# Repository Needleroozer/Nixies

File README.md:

# Nixies

A GitHub repository for collecting various Nixie tube PCB designs and the code that goes with them

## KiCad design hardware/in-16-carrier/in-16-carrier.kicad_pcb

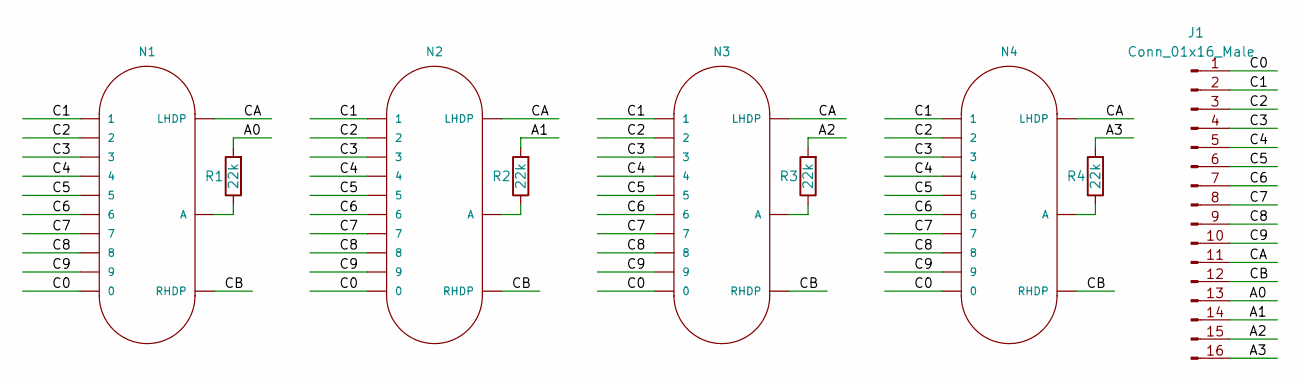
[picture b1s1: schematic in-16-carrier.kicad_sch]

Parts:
J1: Conn_01x16_Male; PinHeader_1x16_P2.54mm_Vertical
N1, N2, N3, N4: IN-16; nixies-us-IN-16
R1, R2, R3, R4: 22k; R_Axial_DIN0207_L6.3mm_D2.5mm_P10.16mm_Horizontal

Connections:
/A0: J1.13, R1.2
/A1: J1.14, R2.2
/A2: J1.15, R3.2
/A3: J1.16, R4.2
/C0: J1.1, N1.0, N2.0, N3.0, N4.0
/C1: J1.2, N1.1, N2.1, N3.1, N4.1
/C2: J1.3, N1.2, N2.2, N3.2, N4.2
/C3: J1.4, N1.3, N2.3, N3.3, N4.3
/C4: J1.5, N1.4, N2.4, N3.4, N4.4
/C5: J1.6, N1.5, N2.5, N3.5, N4.5
/C6: J1.7, N1.6, N2.6, N3.6, N4.6
/C7: J1.8, N1.7, N2.7, N3.7, N4.7
/C8: J1.9, N1.8, N2.8, N3.8, N4.8
/C9: J1.10, N1.9, N2.9, N3.9, N4.9
/CA: J1.11, N1.LHDP, N2.LHDP, N3.LHDP, N4.LHDP
/CB: J1.12, N1.RHDP, N2.RHDP, N3.RHDP, N4.RHDP
unnamed: N1.A, R1.1
unnamed: N2.A, R2.1
unnamed: N3.A, R3.1
unnamed: N4.A, R4.1

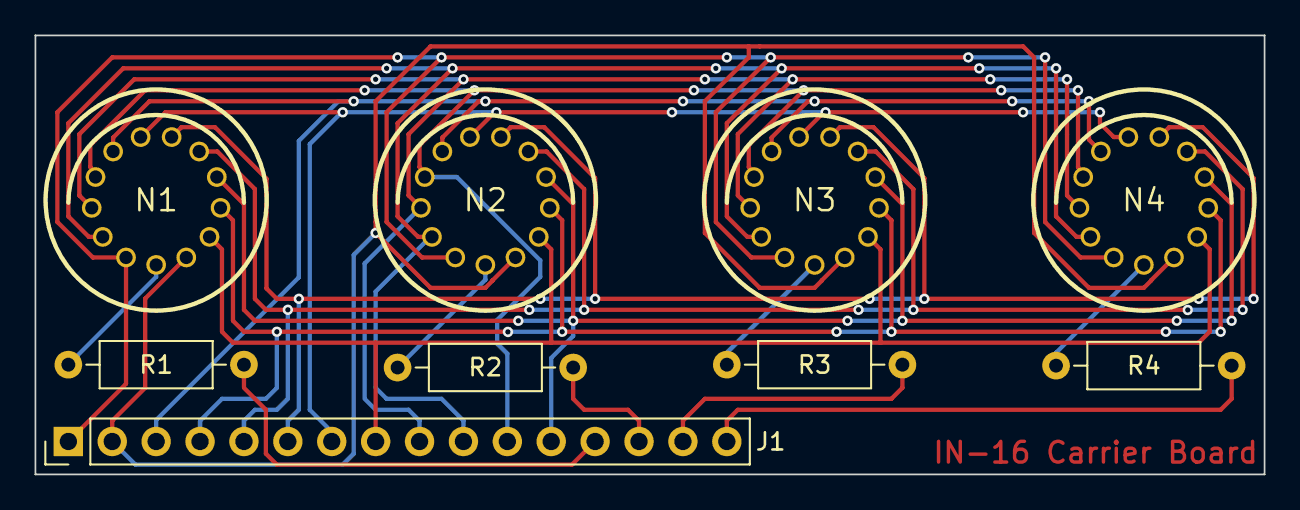
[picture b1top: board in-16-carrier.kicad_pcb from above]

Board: 2 copper layers, 71.1 x 25.4 mm, 9 parts (0 on the bottom side), 20 nets.

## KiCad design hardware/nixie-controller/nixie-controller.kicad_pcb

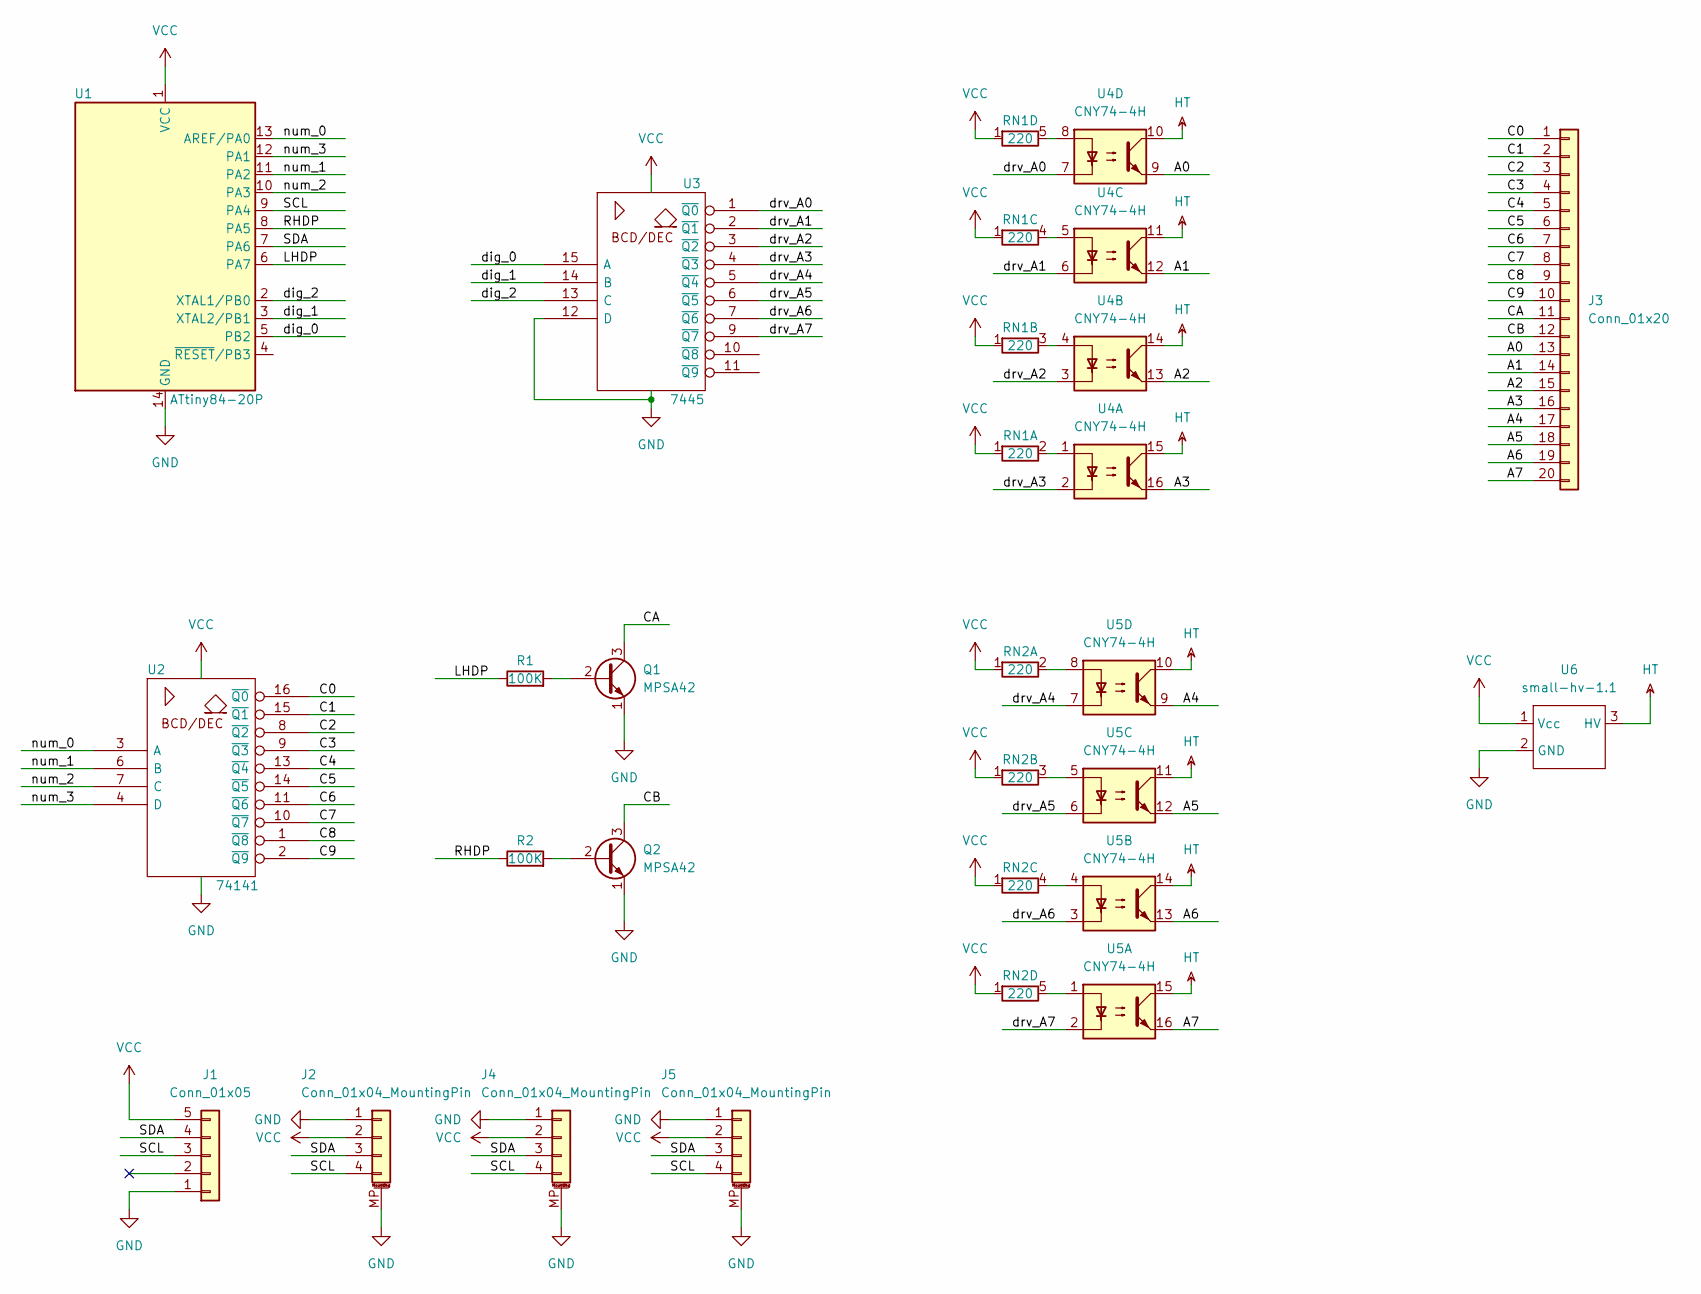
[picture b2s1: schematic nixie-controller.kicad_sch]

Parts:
J1: Conn_01x05; PinHeader_1x05_P2.54mm_Vertical
J2, J4, J5: Conn_01x04_MountingPin; JST_SH_SM04B-SRSS-TB_1x04-1MP_P1.00mm_Horizontal
J3: Conn_01x20; PinSocket_1x20_P2.54mm_Vertical
Q1, Q2: MPSA42; TO-92_Inline_Wide
R1, R2: 100K; R_Axial_DIN0207_L6.3mm_D2.5mm_P10.16mm_Horizontal
RN1, RN2: 220; R_Array_SIP5
U1: ATtiny84-20P; DIP-14_W7.62mm
U2: 74141; DIP-16_W7.62mm
U3: 7445; DIP-16_W7.62mm
U4, U5: CNY74-4H; DIP-16_W7.62mm
U6: small-hv-1.1

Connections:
/A0: J3.13, U4.9
/A1: J3.14, U4.12
/A2: J3.15, U4.13
/A3: J3.16, U4.16
/A4: J3.17, U5.9
/A5: J3.18, U5.12
/A6: J3.19, U5.13
/A7: J3.20, U5.16
/C0: J3.1, U2.16 (~Q0)
/C1: J3.2, U2.15 (~Q1)
/C2: J3.3, U2.8 (~Q2)
/C3: J3.4, U2.9 (~Q3)
/C4: J3.5, U2.13 (~Q4)
/C5: J3.6, U2.14 (~Q5)
/C6: J3.7, U2.11 (~Q6)
/C7: J3.8, U2.10 (~Q7)
/C8: J3.9, U2.1 (~Q8)
/C9: J3.10, U2.2 (~Q9)
/CA: J3.11, Q1.3 (C)
/CB: J3.12, Q2.3 (C)
/LHDP: R1.1, U1.6 (PA7)
/RHDP: R2.1, U1.8 (PA5)
/SCL: J1.3, J2.4, J4.4, J5.4, U1.9 (PA4)
/SDA: J1.4, J2.3, J4.3, J5.3, U1.7 (PA6)
/dig_0: U1.5 (PB2), U3.15 (A)
/dig_1: U1.3 (XTAL2/PB1), U3.14 (B)
/dig_2: U1.2 (XTAL1/PB0), U3.13 (C)
/drv_A0: U3.1 (~Q0), U4.7
/drv_A1: U3.2 (~Q1), U4.6
/drv_A2: U3.3 (~Q2), U4.3
/drv_A3: U3.4 (~Q3), U4.2
/drv_A4: U3.5 (~Q4), U5.7
/drv_A5: U3.6 (~Q5), U5.6
/drv_A6: U3.7 (~Q6), U5.3
/drv_A7: U3.9 (~Q7), U5.2
/num_0: U1.13 (AREF/PA0), U2.3 (A)
/num_1: U1.11 (PA2), U2.6 (B)
/num_2: U1.10 (PA3), U2.7 (C)
/num_3: U1.12 (PA1), U2.4 (D)
GND: J1.1, J2.1, J2.MP (MountPin), J4.1, J4.MP (MountPin), J5.1, J5.MP (MountPin), Q1.1 (E), Q2.1 (E), U1.14 (GND), U2.12 (GND), U3.8 (GND), U3.12 (D), U6.2 (GND)
HT: U4.10, U4.11, U4.14, U4.15, U5.10, U5.11, U5.14, U5.15, U6.3 (HV)
unnamed: Q1.2 (B), R1.2
unnamed: Q2.2 (B), R2.2
unnamed: RN1.2 (R1.2), U4.1
unnamed: RN1.3 (R2.2), U4.4
unnamed: RN1.4 (R3.2), U4.5
unnamed: RN1.5 (R4.2), U4.8
unnamed: RN2.2 (R1.2), U5.8
unnamed: RN2.3 (R2.2), U5.5
unnamed: RN2.4 (R3.2), U5.4
unnamed: RN2.5 (R4.2), U5.1
VCC: J1.5, J2.2, J4.2, J5.2, RN1.1 (R1.1), RN2.1 (R1.1), U1.1 (VCC), U2.5 (VCC), U3.16 (VCC), U6.1 (Vcc)

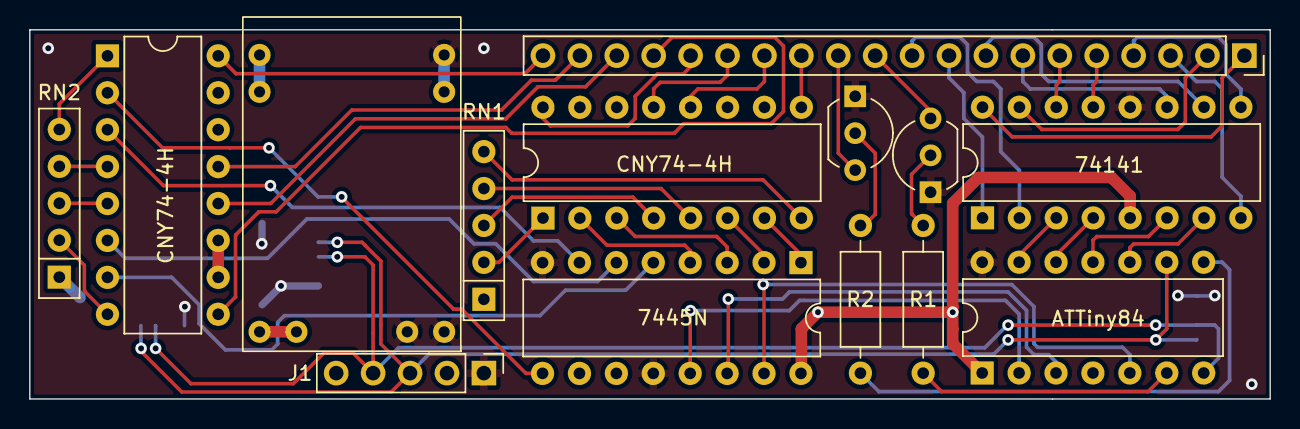
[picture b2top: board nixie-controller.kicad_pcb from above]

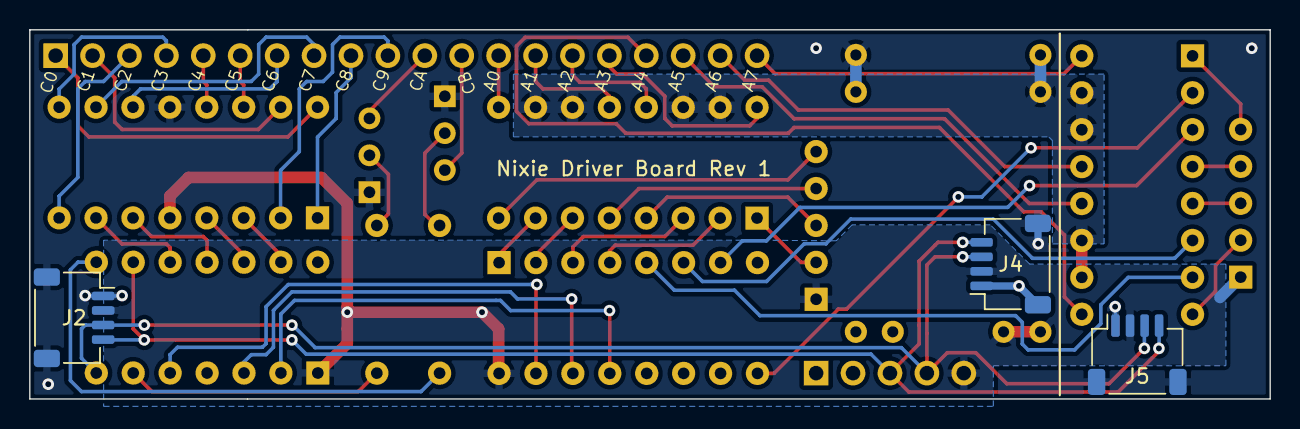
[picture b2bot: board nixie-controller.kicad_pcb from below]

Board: 2 copper layers, 85.3 x 25.4 mm, 17 parts (3 on the bottom side), 52 nets.

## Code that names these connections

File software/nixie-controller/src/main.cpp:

#include <Arduino.h>

// PB0 is bit 2
// PB1 is bit 1
// PB2 is bit 0
#define ENABLE_ANODE(num) (PORTB = (PORTB & ~0x07) | ((num & 0b01) << 2) | (num & 0b010) | ((num & 0b0100) >> 2))

// PA0 is bit 0
// PA1 is bit 3
// PA2 is bit 1
// PA3 is bit 2
#define ENABLE_CATHODE(num) (PORTA = (PORTA & ~0xF0) | ((num & 0b0100) << 1) | ((num & 0b010) << 1) | ((num & 0b1000) >> 2) | (num & 0b01))

#define DISABLE_CATHODES() (PORTA &= 0x50) 

// 7-bit I2C address
#define I2C_SLAVE_ADDRESS 0x4E

struct I2C_Regs_s {
    uint8_t digits[8];
    uint8_t decimals[8];
};

#define REG_SIZE (sizeof(I2C_Regs_s))

volatile union {
    struct I2C_Regs_s regs;
    uint8_t bytes[REG_SIZE];
} i2c_regs = { .regs = {{0xde, 0xad, 0xbe, 0xef, 0xd0, 0xd0, 0xca, 0xfe},
                        {0x01, 0x02, 0x03, 0x04, 0x05, 0x06, 0x07, 0x08}}
};


// decimal points are active-high since we're using NPN transistors
void set_dp(uint8_t val)
{
    switch(val)
    {
        case 1:
            PORTA |= (1 << PA5); // RHDP
            break;
    	case 2:
            PORTA |= (1 << PA7); // LHDP
            break;
        case 3:
            PORTA |= (1 << PA5) | (1 << PA7);
            break;
        default:
            PORTA &= ~((1 << PA5) | (1 << PA7));
    }
}

extern char usi_i2c_slave_address;
extern char* USI_Slave_register_buffer[];


void setup()
{
    for (int i=0; i<REG_SIZE; ++i)
    {
        USI_Slave_register_buffer[i] = (char*) &(i2c_regs.regs[i]);
    }

    usi_i2c_slave_address = I2C_SLAVE_ADDRESS;

    USI_I2C_Init(usi_i2c_slave_address);


    // 1 is output, 0 is input for the DDR* registers
//    DDRA |= 0xAF; // PA7, PA5, PA3:0
//
//    DDRB |= 0x07; // PB2:0
//
//    DISABLE_CATHODES(); // To keep anything from turning on we make sure all the cathodes are off
//
//    ENABLE_ANODE(4); // This is a little jank. Ideally we'd be able to set this to output 8 or 9
//                     // since that doesn't energize anything (or set it to 10+ for output blanking)
//                     // but we don't have the high-bit input line wired to the microcontroller.
//                     // Since this board only has four digits soldered on, enabling digit 4 is perfectly safe
}

void loop()
{

//    uint8_t numbers[] = {7, 10, 9, 10};
//    for (int i=0; i<4; ++i)
//    {
//        if (numbers[i] < 10) ENABLE_ANODE(i); // we get weird anode ghosting across digits otherwise - may just be the breadboard
//        
//        ENABLE_CATHODE(numbers[i]);
//        set_dp(0);
//
//        delay(1); //still has anode ghosting; probably need to mess with anode resistors
//
//        //prevent ghosting onto the next number
//        DISABLE_CATHODES(); 
//    }
}

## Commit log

2023-10-01 Add Markdown docs
2023-10-01 Add symbols and footprints from GitHub
    (converted for newer KiCad .pretty format)
    https://github.com/judge2005/Eagle-and-KiCAD-Nixie-Libs
2023-10-01 Add Nixie Controller hardware design
2023-10-01 Add IN-16 carrier board
2023-10-06 Add Panelization submodule
2023-10-06 Finish routing breakaway version, add gerbers
2023-10-06 Add 3-high panelized version for 100x100mm JLCPCB panels
2024-02-25 Add ATTiny84 blinky with PlatformIO and ArduinoISP
2024-02-26 Create functional multiplexing routine
2024-02-26 Set fuses for 8MHz clock
    Also only enable anodes for active digits to mitigate ghosting problems
2024-02-27 Bad I2C slave code (barely works)
2024-03-02 Pull USI I2C files from GitHub
    https://github.com/CalcProgrammer1/Stepper-Motor-Controller/tree/master/UnipolarStepperDriver
2024-03-02 Address multi-byte data send bug
    https://github.com/CalcProgrammer1/Stepper-Motor-Controller/issues/3
2024-03-03 First crack at usi_i2c library integration
